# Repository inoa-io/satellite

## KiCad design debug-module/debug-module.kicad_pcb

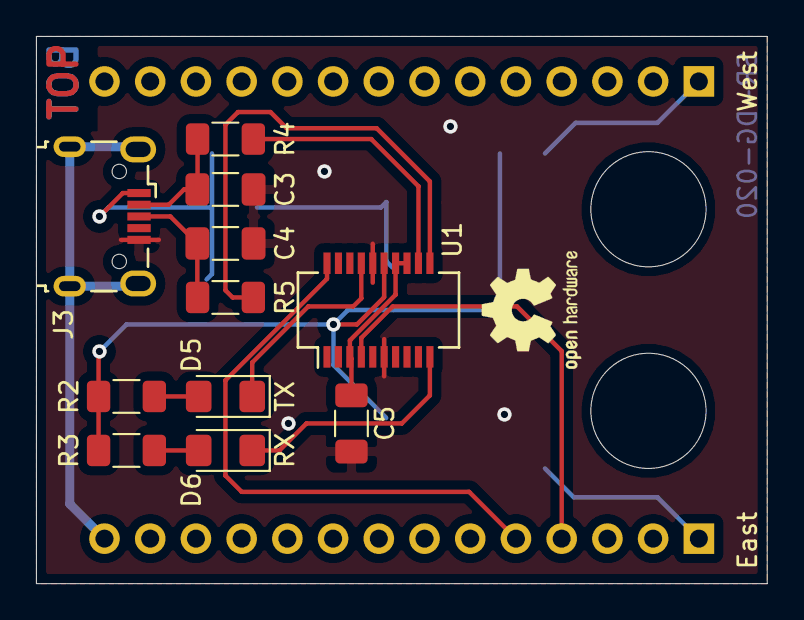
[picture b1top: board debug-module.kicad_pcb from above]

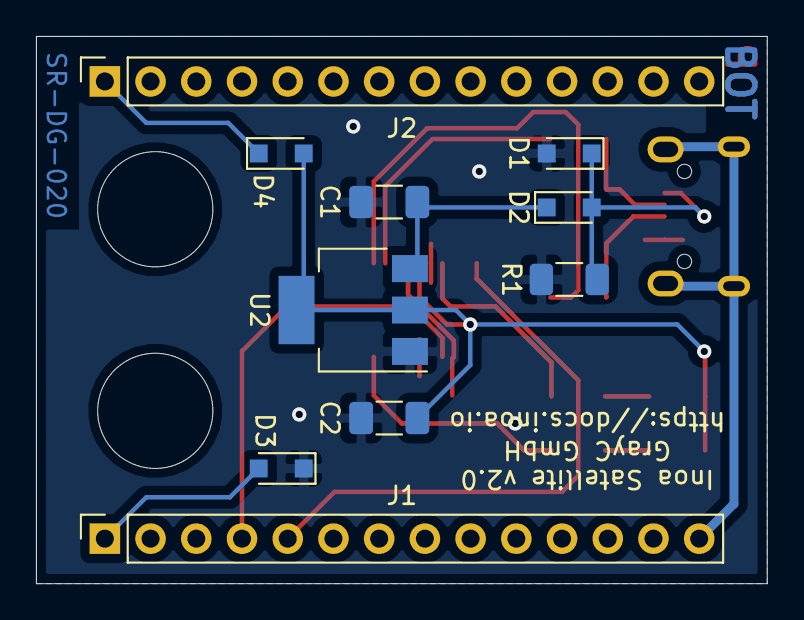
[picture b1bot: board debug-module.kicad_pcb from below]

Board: 2 copper layers, 40.6 x 30.4 mm, 25 parts (11 on the bottom side), 18 nets.

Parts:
C1, C5: 100nF; C_1206_3216Metric_Pad1.33x1.80mm_HandSolder
C2: 10uF; C_1206_3216Metric_Pad1.33x1.80mm_HandSolder
C3, C4: 47pF; C_1206_3216Metric_Pad1.33x1.80mm_HandSolder
D1: BZT52C6V2; D_SOD-323_HandSoldering
D2: 1N5819; D_SOD-323_HandSoldering
D3, D4: D_Schottky; D_SOD-323_HandSoldering
D5: TX; LED_1206_3216Metric_Pad1.42x1.75mm_HandSolder
D6: RX; LED_1206_3216Metric_Pad1.42x1.75mm_HandSolder
G1: LOGO; grayc-logo-negative
G2: Logo_Open_Hardware_Small; OSHW-Logo2_7.3x6mm_SilkScreen
H1: Reset; MountingHole_6.4mm_M6
H2: Status; MountingHole_6.4mm_M6
J1: East; PinSocket_1x14_P2.54mm_Vertical
J2: West; PinSocket_1x14_P2.54mm_Vertical
J3: USB_B_Micro; USB_Micro-B_Wuerth_629105150521
R1: 10k; R_1206_3216Metric_Pad1.30x1.75mm_HandSolder
R2, R3: 220R; R_1206_3216Metric_Pad1.30x1.75mm_HandSolder
R4, R5: 27R; R_1206_3216Metric_Pad1.30x1.75mm_HandSolder
U1: FT231XS; SSOP-20_3.9x8.7mm_P0.635mm
U2: LD1117S33; SOT-223-3_TabPin2

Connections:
+3V3: C2.1, D4.2, R2.1, R3.1, U1.15, U2.2
GND: C1.2, C2.2, C3.2, C4.2, C5.2, D1.2, D3.1, J3.5, R1.2, U1.6, U1.16, U2.1
GNDPWR: J1.14, J3.6
unnamed: C1.1, D2.1, U2.3
unnamed: C5.1, U1.3, U1.13, U1.14
unnamed: D1.1, D2.2, J3.1, R1.1
unnamed: D3.2, J1.1
unnamed: D4.1, J2.1
unnamed: D5.2, R2.2
unnamed: D6.2, R3.2
unnamed: R4.1, U1.12
unnamed: R5.1, U1.11
RX_LED: D6.1, U1.10
TX_LED: D5.1, U1.17
U0RXD: J1.5, U1.20
U0TXD: J1.4, U1.4
USB_DM: C3.1, J3.2, R4.2
USB_DP: C4.1, J3.3, R5.2

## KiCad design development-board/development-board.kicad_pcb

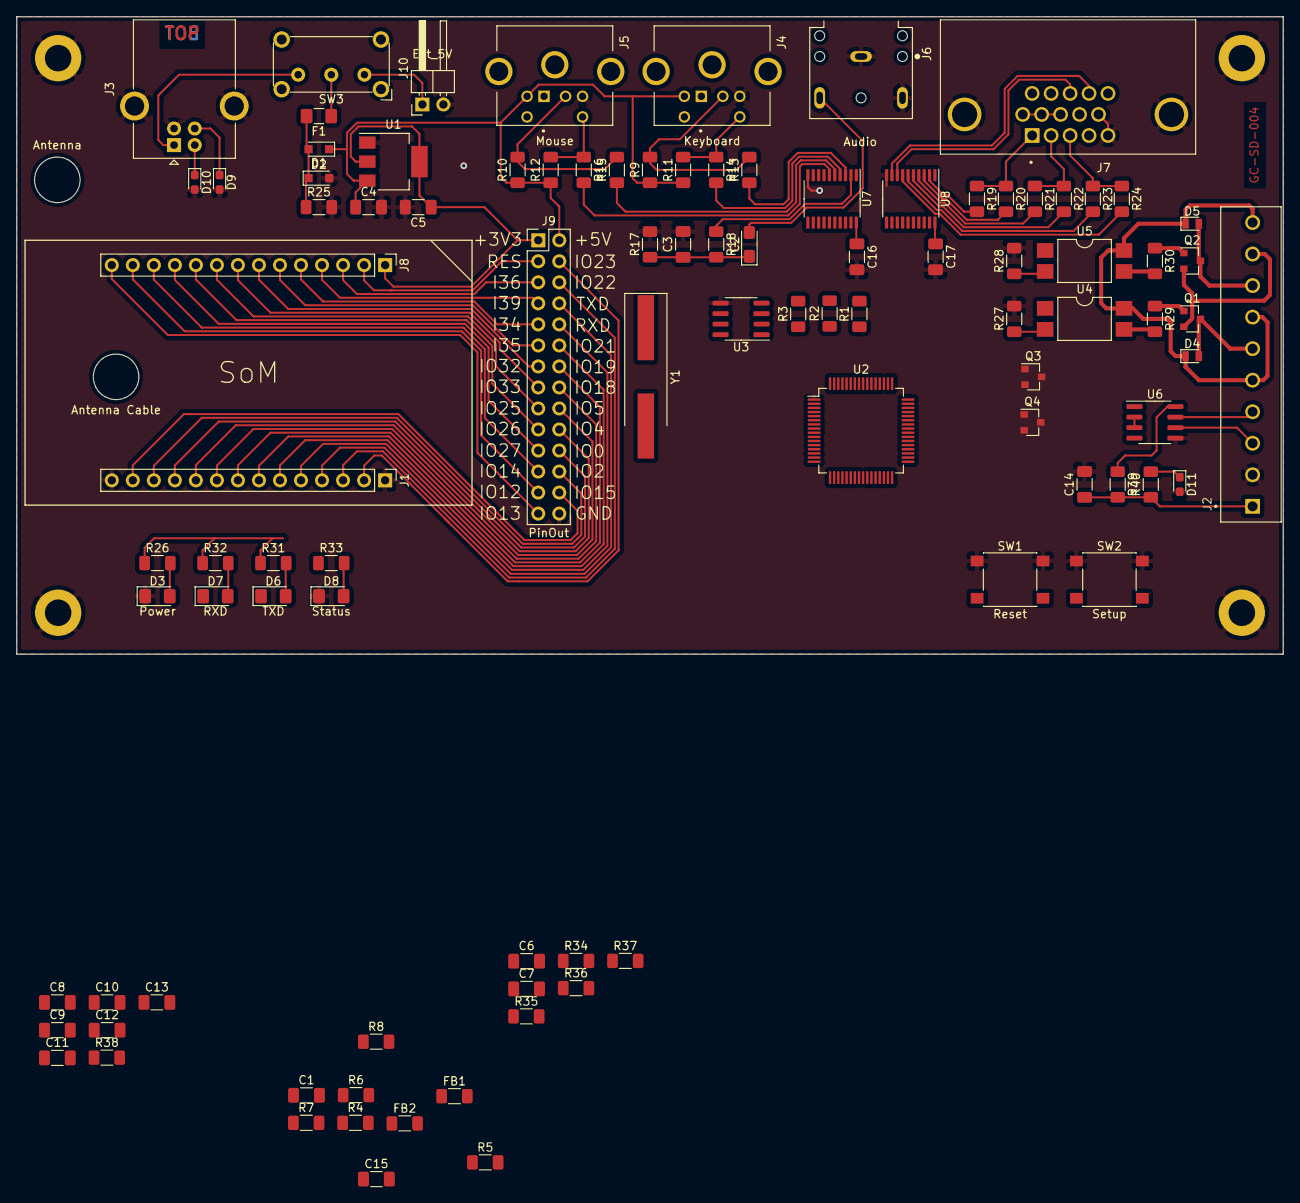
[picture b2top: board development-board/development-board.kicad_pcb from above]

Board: 2 copper layers, 153.0 x 77.0 mm, 103 parts (0 on the bottom side), 95 nets.

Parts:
C1, C3, C4, C14, C15, C16, C17: 100nF; C_1206_3216Metric_Pad1.33x1.80mm_HandSolder
C2: 10uF; CP_EIA-3216-18_Kemet-A_Pad1.58x1.35mm_HandSolder
C5: 10uF; C_1206_3216Metric_Pad1.33x1.80mm_HandSolder
C6, C7: C; C_1206_3216Metric_Pad1.33x1.80mm_HandSolder
C8, C9: 12pF; C_1206_3216Metric_Pad1.33x1.80mm_HandSolder
C10, C12: 4u7; C_1206_3216Metric_Pad1.33x1.80mm_HandSolder
C11, C13: 0u1; C_1206_3216Metric_Pad1.33x1.80mm_HandSolder
D1: BZT52C6V2; D_SOD-323_HandSoldering
D2: 1N5819; D_SOD-323_HandSoldering
D3: Power; LED_1206_3216Metric_Pad1.42x1.75mm_HandSolder
D4, D5: BAV303; D_MicroMELF
D6: TXD; LED_1206_3216Metric_Pad1.42x1.75mm_HandSolder
D7: RXD; LED_1206_3216Metric_Pad1.42x1.75mm_HandSolder
D8: Status; LED_1206_3216Metric_Pad1.42x1.75mm_HandSolder
D9, D10, D11: D_TVS; D_0603_1608Metric_Pad1.05x0.95mm_HandSolder
F1: 6V/800mA; Fuse_1206_3216Metric_Pad1.42x1.75mm_HandSolder
FB1, FB2: 1k@100MHz; R_1206_3216Metric_Pad1.30x1.75mm_HandSolder
H1, H2, H3, H4: MountingHole_Pad; MountingHole_3.2mm_M3_DIN965_Pad
H5: Antenna Cable; MountingHole_5.5mm
H6: Antenna; MountingHole_5.5mm
J1: East; PinHeader_1x14_P2.54mm_Vertical
J2: Screw_Terminal; TE_1-1776113-0
J3: USB_B; USB_B_OST_USB-B1HSxx_Horizontal
J4: Keyboard; TE_5749180-1
J5: Mouse; TE_5749180-1
J6: Audio; CUI_SJ1-3523N
J7: VGA; AMPHENOL_L77HDE15SD1CH4F
J8: West; PinHeader_1x14_P2.54mm_Vertical
J9: PinOut; PinHeader_2x14_P2.54mm_Vertical
J10: Ext_5V; PinHeader_1x02_P2.54mm_Horizontal
Q1, Q2: MMBT3904; SOT-23
Q3, Q4: S8050; SOT-23
R1, R2, R3: 33R; R_1206_3216Metric_Pad1.30x1.75mm_HandSolder
R4, R5, R7, R25, R34, R35, R36, R37: 10k; R_1206_3216Metric_Pad1.30x1.75mm_HandSolder
R6: 2k2; R_1206_3216Metric_Pad1.30x1.75mm_HandSolder
R8: 0R; R_1206_3216Metric_Pad1.30x1.75mm_HandSolder
R9, R10, R11, R12: 2k; R_1206_3216Metric_Pad1.30x1.75mm_HandSolder
R13, R14, R15, R16: 120R; R_1206_3216Metric_Pad1.30x1.75mm_HandSolder
R17: 150R; R_1206_3216Metric_Pad1.30x1.75mm_HandSolder
R18: 270R; R_1206_3216Metric_Pad1.30x1.75mm_HandSolder
R19, R21, R23: 400R; R_1206_3216Metric_Pad1.30x1.75mm_HandSolder
R20, R22, R24: 800R; R_1206_3216Metric_Pad1.30x1.75mm_HandSolder
R26, R27, R28, R29, R30, R31, R32, R33: 220R; R_1206_3216Metric_Pad1.30x1.75mm_HandSolder
R38: 12k; R_1206_3216Metric_Pad1.30x1.75mm_HandSolder
R39, R40: R; R_1206_3216Metric_Pad1.30x1.75mm_HandSolder
SW1: Reset; SW_SPST_PTS645
SW2: Setup; SW_SPST_PTS645
SW3: Power; SW_E-Switch_EG1224_SPDT_Angled
U1: LD1117S33; SOT-223-3_TabPin2
U2: FT2232HL; LQFP-64_10x10mm_P0.5mm
U3: 93C46-WMN6TP; SOIC-8_3.9x4.9mm_P1.27mm
U4, U5: LTV-817S; SMDIP-4_W9.53mm
U6: MAX3486; SOIC-8_3.9x4.9mm_P1.27mm
U7, U8: SN74CBT16292; TSSOP-20_4.4x6.5mm_P0.65mm
Y1: 12MHz; Crystal_SMD_HC49-SD_HandSoldering

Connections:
+3V3: C1.1, C5.1, C15.1, C16.1, C17.1, FB1.1, FB2.2, J8.1, J9.1, R4.2, R5.2, R7.2, R8.1, R26.1, R31.1, R32.1, R34.1, R35.1, R39.1, U1.2, U3.8, U6.8, U7.20, U8.20
+5V: C4.1, D2.1, J4.3, J5.3, J9.2, R9.1, R10.1, R11.1, R12.1, U1.3
Blue_High: R23.2, U8.6
Blue_Low: R24.2, U8.7
Chip_PU: C6.1, J8.2, J9.3, Q4.3, R34.2, SW1.2
EECLK: R2.1, R5.1, U3.2
EECS: R1.1, R4.1, U3.1
EEDATA: R3.1, R6.1, U3.3
FT_~DTR~: Q3.1, R37.1, U2.43
FT_~RTS~: Q4.1, R36.2, U2.40
GND: C1.2, C3.2, C4.2, C5.2, C6.2, C7.2, C8.2, C9.2, C10.2, C11.2, C12.2, C13.2, C14.2, C15.2, C16.2, C17.2, D1.2, D3.1, D8.1, D9.2, D10.2, D11.2, H1.1, H2.1, H3.1, H4.1, J1.1, J1.14, J2.2, J3.4, J3.5, J4.4, J5.4, J6.1, J6.3, J7.0, J7.5, J7.6, J7.7, J7.8, J7.10, J9.28, J10.2, R17.2, R25.2, R27.2, R28.2, R38.2, SW1.1, SW2.1, U1.1, U2.1, U2.5, U2.10, U2.11, U2.13, U2.15, U2.25, U2.35, U2.47, U2.51, U3.5, U6.5, U7.10, U8.10
GND2: J2.9, Q1.2, Q2.2
Green_High: R21.2, U8.4
Green_Low: R22.2, U8.5
HSync: J7.13, U8.8
I34: J8.5, J9.9
I35: J8.6, J9.11
I36: J8.3, J9.5
I39: J8.4, J9.7
IO0: C7.1, J1.11, J9.22, Q3.3, R35.2, SW2.2
IO2: J1.12, J9.24
IO4: J1.10, J9.20, U8.13
IO5: J1.9, J9.18, U8.14
IO12: J8.13, J9.25
IO13: J8.14, J9.27, R33.1
IO14: J8.12, J9.23
IO15: J1.13, J9.26, U8.11
IO18: J1.8, J9.16, U8.15
IO19: J1.7, J9.14, U8.16
IO21: J1.6, J9.12, U8.17
IO22: J1.3, J9.6, U8.18
IO23: J1.2, J9.4, U8.12
IO25: J8.9, J9.17, U7.18
IO26: J8.10, J9.19, U7.15
IO27: J8.11, J9.21, U7.14
IO32: J8.7, J9.13, U7.16
IO33: J8.8, J9.15, U7.17
unnamed: C2.1, C3.1, R17.1, R18.2
unnamed: C2.2, J6.2
unnamed: C8.1, U2.2, Y1.1
unnamed: C9.1, U2.3, Y1.2
unnamed: C10.1, C11.1, FB2.1, U2.4
unnamed: C12.1, C13.1, FB1.2, U2.9
unnamed: D1.1, D2.2, F1.2, R25.1
unnamed: D3.2, R26.2
unnamed: D6.2, R31.2
unnamed: D7.2, R32.2
unnamed: D8.2, R33.2
unnamed: D11.1, R40.2
unnamed: F1.1, SW3.2
unnamed: J4.2, R9.2, R13.2
unnamed: J4.6, R11.2, R14.1
unnamed: J5.2, R10.2, R15.2
unnamed: J5.6, R12.2, R16.1
unnamed: J7.1, R19.1, R20.1
unnamed: J7.2, R21.1, R22.1
unnamed: J7.3, R23.1, R24.1
unnamed: J10.1, SW3.1
unnamed: Q1.1, R29.1
unnamed: Q2.1, R30.1
unnamed: Q3.2, R36.1
unnamed: Q4.2, R37.2
unnamed: R1.2, U2.63
unnamed: R2.2, U2.62
unnamed: R3.2, U2.61
unnamed: R6.2, R7.1, U3.4
unnamed: R8.2, U3.6
unnamed: R27.1, U4.2
unnamed: R28.1, U5.2
unnamed: R29.2, U4.3
unnamed: R30.2, U5.3
unnamed: R38.1, U2.6
PC_Enable: U7.19, U8.19
PS2_0_Clock: R13.1, U7.3
PS2_0_Data: R14.2, U7.4
PS2_1_Clock: R15.1, U7.5
PS2_1_Data: R16.2, U7.6
RS485_A: J2.3, U6.6
RS485_B: J2.4, U6.7
RS485_TXE: U6.2, U6.3
RX_LED: D7.1, U2.54
Red_High: R19.2, U8.2
Red_Low: R20.2, U8.3
Relay_In_0: D4.2, J2.6, Q1.3
Relay_In_1: D5.2, J2.8, Q2.3
S0: C14.1, J2.1, R39.2, R40.1
Speaker: R18.1, U7.2
TX_LED: D6.1, U2.55
U0RXD: J1.5, J9.10
U0TXD: J1.4, J9.8
USB_DN: D10.1, J3.2, U2.7
USB_DP: D9.1, J3.3, U2.8
VBUS: J3.1, SW3.3
VS: D4.1, D5.1, J2.5, J2.7, J2.10, U4.4, U5.4
VSync: J7.14, U8.9

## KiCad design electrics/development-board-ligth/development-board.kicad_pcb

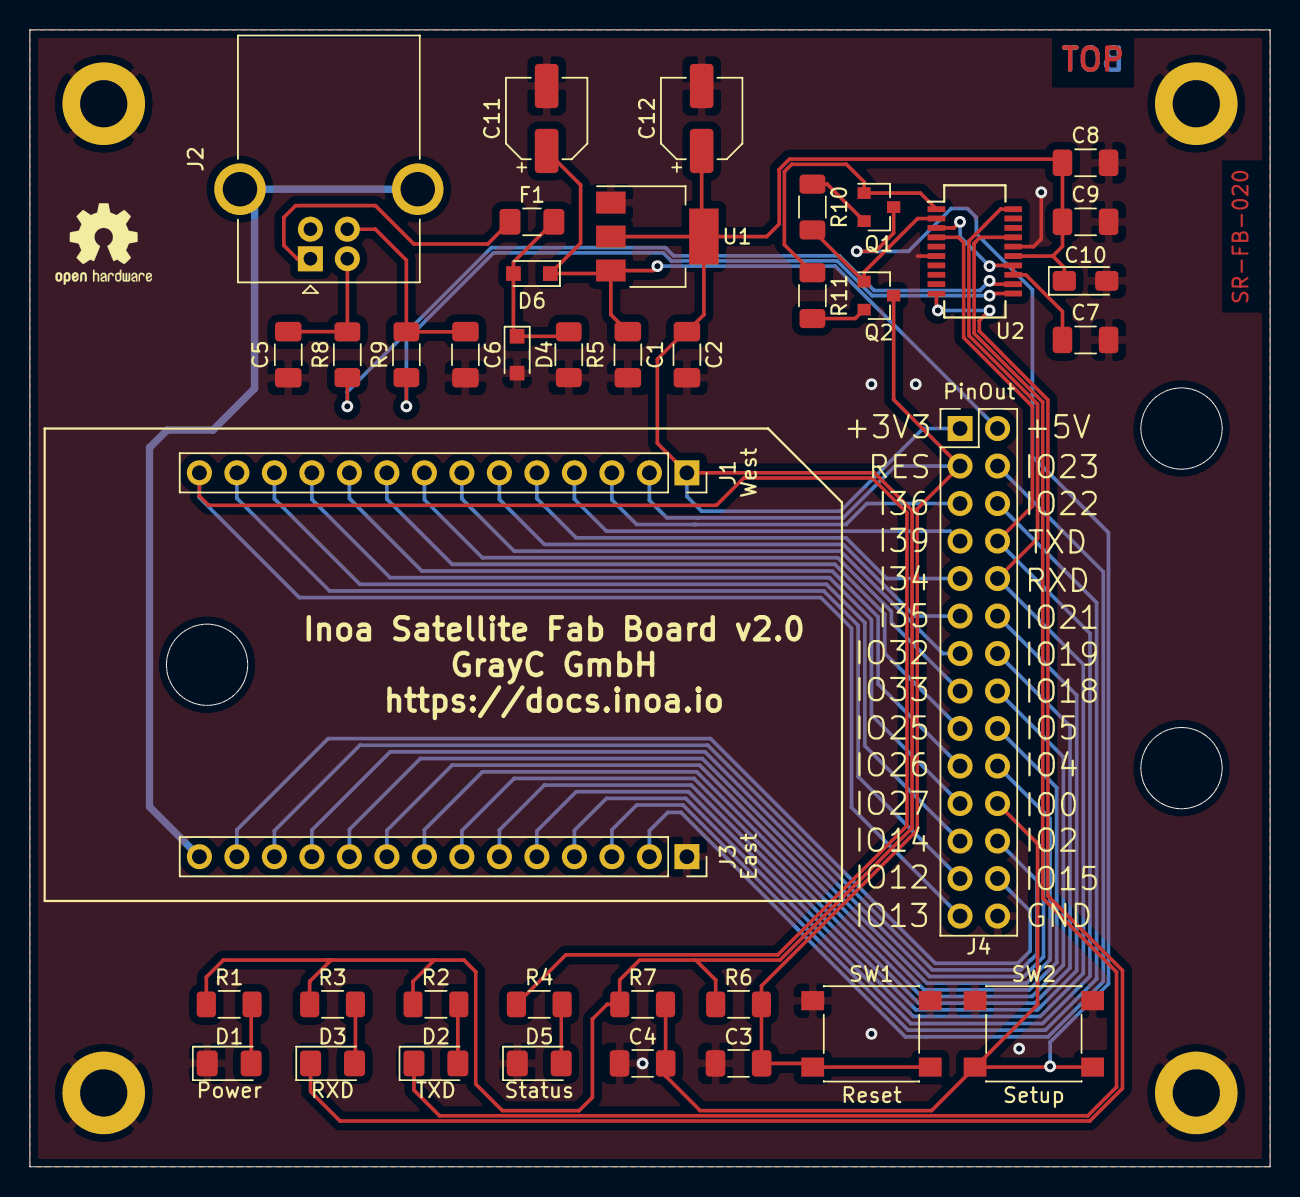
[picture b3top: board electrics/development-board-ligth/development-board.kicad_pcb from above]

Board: 2 copper layers, 84.0 x 77.0 mm, 49 parts (0 on the bottom side), 46 nets.

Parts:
C1, C7, C8, C9: 100nF; C_1206_3216Metric_Pad1.33x1.80mm_HandSolder
C2: 10uF; C_1206_3216Metric_Pad1.33x1.80mm_HandSolder
C3, C4: 1nF; C_1206_3216Metric_Pad1.33x1.80mm_HandSolder
C5, C6: 47pF; C_1206_3216Metric_Pad1.33x1.80mm_HandSolder
C10: 4u7; CP_EIA-3216-18_Kemet-A_Pad1.58x1.35mm_HandSolder
C11: 100uF; CP_Elec_5x5.3
C12: 47uF; CP_Elec_5x5.3
D1: Power; LED_1206_3216Metric_Pad1.42x1.75mm_HandSolder
D2: TXD; LED_1206_3216Metric_Pad1.42x1.75mm_HandSolder
D3: RXD; LED_1206_3216Metric_Pad1.42x1.75mm_HandSolder
D4: BZT52C6V2; D_SOD-323_HandSoldering
D5: Status; LED_1206_3216Metric_Pad1.42x1.75mm_HandSolder
D6: 1N5819; D_SOD-323_HandSoldering
F1: 6V/800mA; Fuse_1206_3216Metric_Pad1.42x1.75mm_HandSolder
H1: WiFi Cable; MountingHole_5.5mm
H2, H3, H5, H7: MountingHole_Pad; MountingHole_3.2mm_M3_DIN965_Pad
H4, H6: Antenna; MountingHole_5.5mm
J1: West; PinSocket_1x14_P2.54mm_Vertical
J2: USB_B; USB_B_OST_USB-B1HSxx_Horizontal
J3: East; PinSocket_1x14_P2.54mm_Vertical
J4: PinOut; PinHeader_2x14_P2.54mm_Vertical
LOGO1: Logo_Open_Hardware_Small; OSHW-Logo2_7.3x6mm_SilkScreen
LOGO2: LOGO; grayc-logo-negative
Q1, Q2: S8050; SOT-23
R1, R2, R3, R4: 220R; R_1206_3216Metric_Pad1.30x1.75mm_HandSolder
R5, R6, R7, R10, R11: 10k; R_1206_3216Metric_Pad1.30x1.75mm_HandSolder
R8, R9: 27R; R_1206_3216Metric_Pad1.30x1.75mm_HandSolder
SW1: Reset; SW_SPST_PTS645
SW2: Setup; SW_SPST_PTS645
U1: LD1117S33; SOT-223-3_TabPin2
U2: FT231XS; SSOP-20_3.9x8.7mm_P0.635mm

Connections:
+3V3: C2.1, C8.1, C9.1, C10.1, C12.1, J1.1, J4.1, R1.1, R2.1, R3.1, R6.1, R7.1, U1.2, U2.15
+5V: C1.1, C11.1, D6.1, J4.2, U1.3
Chip_PU: C3.1, J1.2, J4.3, Q2.3, R6.2, SW1.2
FT_~DTR: Q1.1, R11.1, U2.1
FT_~RTS: Q2.1, R10.2, U2.2
GND: C1.2, C2.2, C3.2, C4.2, C5.2, C6.2, C7.2, C8.2, C9.2, C10.2, C11.2, C12.2, D1.1, D4.2, D5.1, H2.1, H3.1, H5.1, H7.1, J2.4, J3.1, J4.28, R5.2, SW1.1, SW2.1, U1.1, U2.6, U2.16
GNDPWR: J2.5, J3.14
I34: J1.5, J4.9
I35: J1.6, J4.11
I36: J1.3, J4.5
I39: J1.4, J4.7
IO0: C4.1, J3.11, J4.22, Q1.3, R7.2, SW2.2
IO2: J3.12, J4.24
IO4: J3.10, J4.20
IO5: J3.9, J4.18
IO12: J1.13, J4.25
IO13: J1.14, J4.27, R4.1
IO14: J1.12, J4.23
IO15: J3.13, J4.26
IO18: J3.8, J4.16
IO19: J3.7, J4.14
IO21: J3.6, J4.12
IO22: J3.3, J4.6
IO23: J3.2, J4.4
IO25: J1.9, J4.17
IO26: J1.10, J4.19
IO27: J1.11, J4.21
IO32: J1.7, J4.13
IO33: J1.8, J4.15
unnamed: C7.1, U2.3, U2.13, U2.14
unnamed: D1.2, R1.2
unnamed: D2.2, R2.2
unnamed: D3.2, R3.2
unnamed: D4.1, D6.2, F1.2, R5.1
unnamed: D5.2, R4.2
unnamed: Q1.2, R10.1
unnamed: Q2.2, R11.2
unnamed: R8.1, U2.12
unnamed: R9.1, U2.11
RX_LED: D3.1, U2.10
TX_LED: D2.1, U2.17
U0RXD: J3.5, J4.10, U2.20
U0TXD: J3.4, J4.8, U2.4
USB_DM: C5.1, J2.2, R8.2
USB_DP: C6.1, J2.3, R9.2
VBUS: F1.1, J2.1

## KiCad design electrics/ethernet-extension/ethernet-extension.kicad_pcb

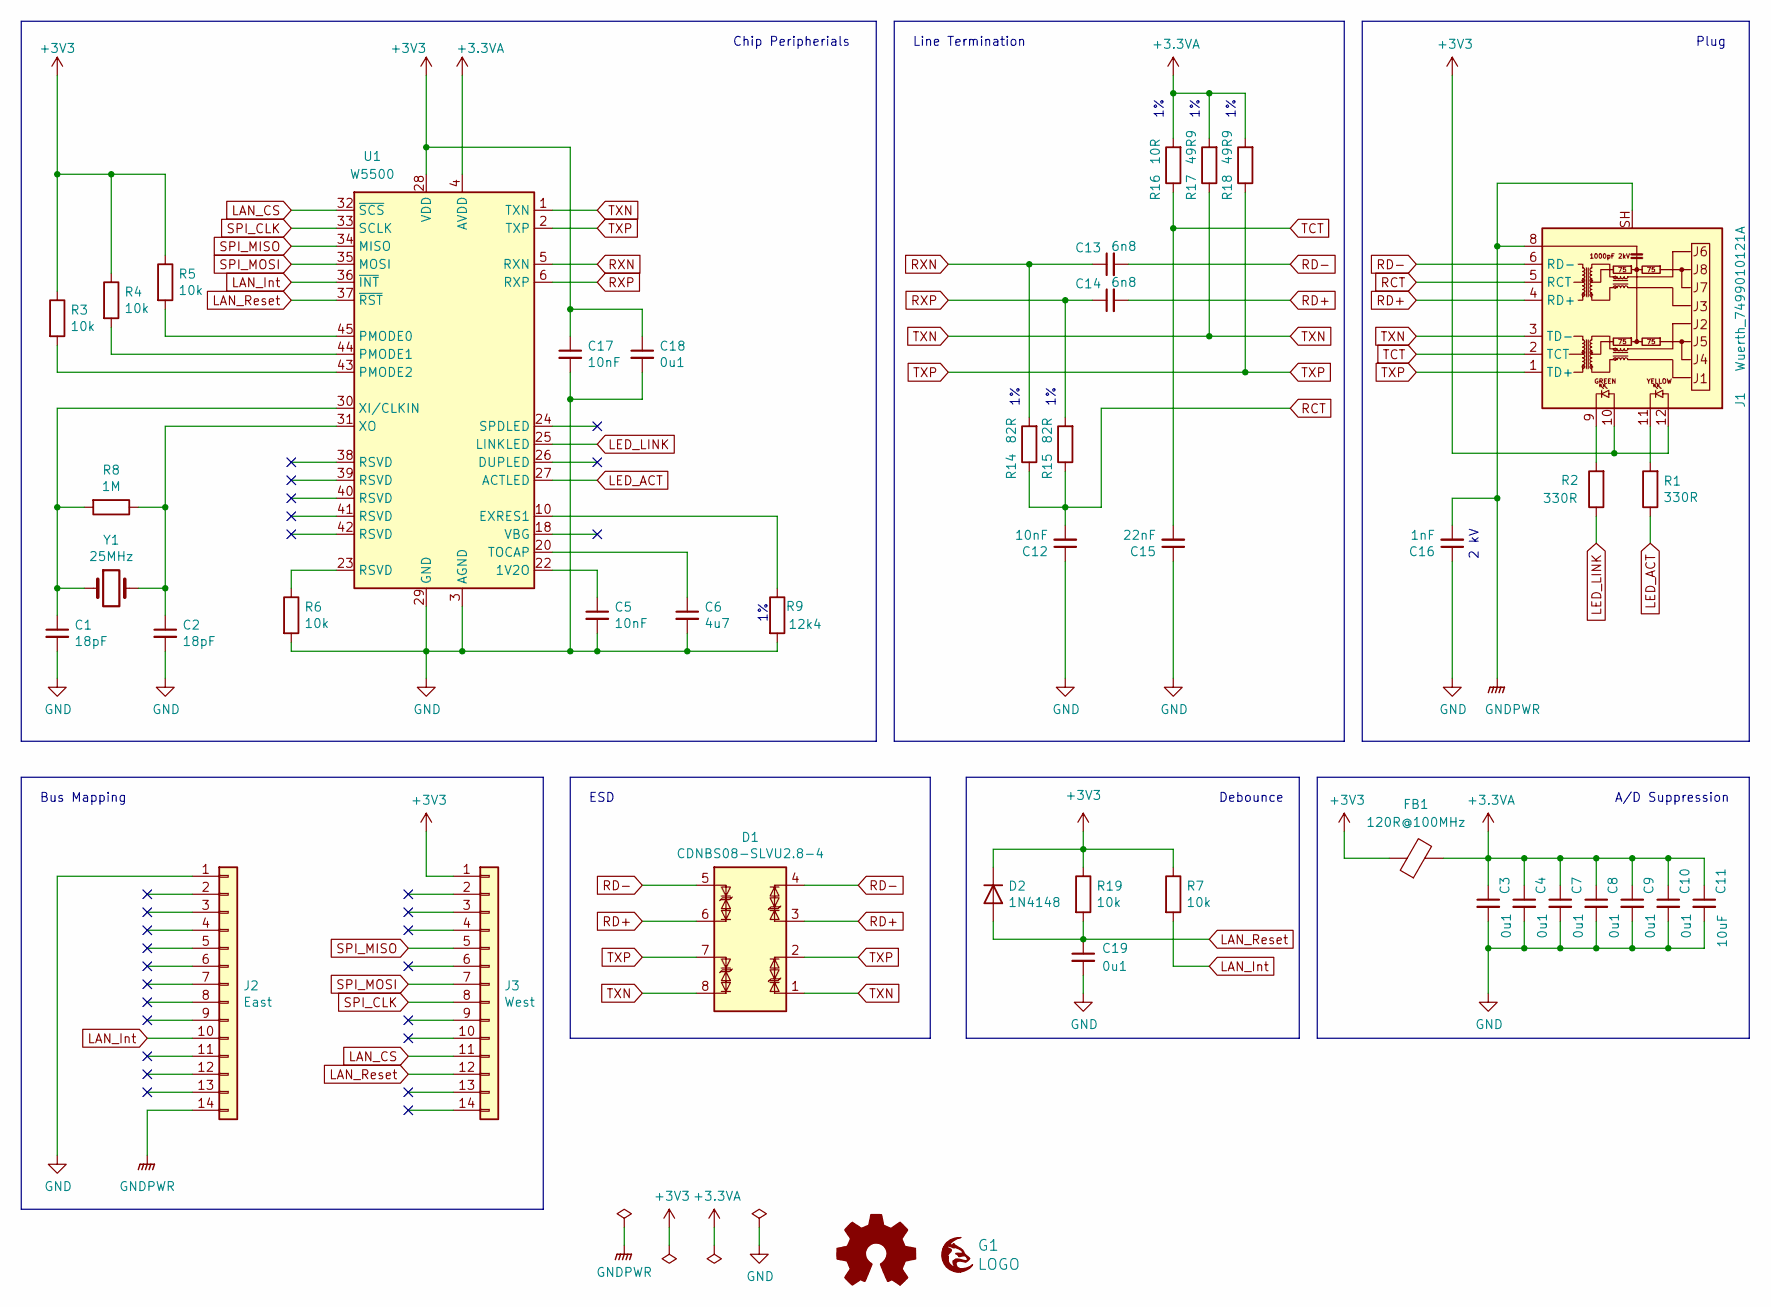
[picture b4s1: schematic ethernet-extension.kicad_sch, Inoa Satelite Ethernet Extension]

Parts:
C1, C2: 18pF; C_0603_1608Metric_Pad1.08x0.95mm_HandSolder; mouser# 581-06035A180JAT4A
C3, C4, C7, C8, C9, C10, C18, C19: 0u1; C_0603_1608Metric_Pad1.08x0.95mm_HandSolder; mouser# 80-C0603C104M4R
C5, C12, C17: 10nF; C_0603_1608Metric_Pad1.08x0.95mm_HandSolder; mouser# 581-06031C103K4T2A
C6: 4u7; C_0603_1608Metric_Pad1.08x0.95mm_HandSolder; mouser# 187-CL10A475MQ8NNNC
C11: 10uF; C_0603_1608Metric_Pad1.08x0.95mm_HandSolder; mouser# 187-CL10A106MQ8NNNC
C13, C14: 6n8; C_0603_1608Metric_Pad1.08x0.95mm_HandSolder; mouser# 80-C0603C682K5R
C15: 22nF; C_0603_1608Metric_Pad1.08x0.95mm_HandSolder; mouser# 187-CL10B223KB8NNNC
C16: 1nF; C_1812_4532Metric_Pad1.57x3.40mm_HandSolder; mouser# 80-C1812C103KGR
D1: CDNBS08-SLVU2.8-4; SOIC-8_3.9x4.9mm_P1.27mm; mouser# 652-CDNBS08SLVU2.8-4
D2: 1N4148; D_SOD-323_HandSoldering; mouser# 241-1N4148WSR100001
FB1: 120R@100MHz; L_0805_2012Metric; mouser# 652-MG2029-121Y
G1: LOGO; grayc-logo-negative
G2: Logo_Open_Hardware_Small; OSHW-Logo2_7.3x6mm_SilkScreen
J1: Wuerth_7499010121A; RJ45_Wuerth_7499010121A_Horizontal; mouser# 710-7499010121A
J2: East; PinHeader_1x14_P2.54mm_Vertical; mouser# 437-8018701453001101
J3: West; PinHeader_1x14_P2.54mm_Vertical; mouser# 437-8018701453001101
R1, R2: 330R; R_0603_1608Metric_Pad0.98x0.95mm_HandSolder; mouser# 652-CR0603FX-3300ELF
R3, R4, R5, R6, R7, R19: 10k; R_0603_1608Metric_Pad0.98x0.95mm_HandSolder; mouser# 652-CR0603AFX1002EAS
R8: 1M; R_0603_1608Metric_Pad0.98x0.95mm_HandSolder; mouser# 652-CMP0603-FX-1004L
R9: 12k4; R_0603_1608Metric_Pad0.98x0.95mm_HandSolder; mouser# 652-CR0603FX-1242ELF
R14, R15: 82R; R_0603_1608Metric_Pad0.98x0.95mm_HandSolder; mouser# 667-ERJ-3EKF82R0V
R16: 10R; R_0603_1608Metric_Pad0.98x0.95mm_HandSolder; mouser# 603-RC0603FR-1310RL
R17, R18: 49R9; R_0603_1608Metric_Pad0.98x0.95mm_HandSolder; mouser# 667-ERJ-3EKF49R9V
U1: W5500; LQFP-48_7x7mm_P0.5mm; mouser# 950-W5500
Y1: 25MHz; Crystal_SMD_0603-2Pin_6.0x3.5mm_HandSoldering; mouser# 520-250-18-23A

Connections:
+3.3VA: C3.1, C4.1, C7.1, C8.1, C9.1, C10.1, C11.1, FB1.2, R16.2, R17.2, R18.2, U1.4 (AVDD), U1.8 (AVDD), U1.11 (AVDD), U1.15 (AVDD), U1.17 (AVDD), U1.21 (AVDD)
+3V3: C17.1, C18.1, D2.1 (K), FB1.1, J1.10, J1.12, J3.1, R3.1, R4.1, R5.1, R7.1, R19.1, U1.28 (VDD)
GND: C1.2, C2.2, C3.2, C4.2, C5.2, C6.2, C7.2, C8.2, C9.2, C10.2, C11.2, C12.1, C15.1, C16.1, C17.2, C18.2, C19.2, J2.1, R6.2, R9.2, U1.3 (AGND), U1.9 (AGND), U1.14 (AGND), U1.16 (AGND), U1.19 (AGND), U1.29 (GND), U1.48 (AGND)
GNDPWR: C16.2, J1.8, J1.SH, J2.14
LAN_CS: J3.11, U1.32 (~SCS)
LAN_Int: J2.10, R7.2, U1.36 (~INT)
LAN_Reset: C19.1, D2.2 (A), J3.12, R19.2, U1.37 (~RST)
LED_ACT: R1.1, U1.27 (ACTLED)
LED_LINK: R2.1, U1.25 (LINKLED)
unnamed: C1.1, R8.2, U1.30 (XI/CLKIN), Y1.1
unnamed: C2.1, R8.1, U1.31 (XO), Y1.2
unnamed: C5.1, U1.22 (1V2O)
unnamed: C6.1, U1.20 (TOCAP)
unnamed: J1.9, R2.2
unnamed: J1.11, R1.2
unnamed: R3.2, U1.43 (PMODE2)
unnamed: R4.2, U1.44 (PMODE1)
unnamed: R5.2, U1.45 (PMODE0)
unnamed: R6.1, U1.23 (RSVD)
unnamed: R9.1, U1.10 (EXRES1)
RCT: C12.2, J1.5 (RCT), R14.1, R15.1
RD+: C14.2, D1.3 (TVS1), D1.6 (TVS2), J1.4 (RD+)
RD-: C13.2, D1.4 (TVS2), D1.5 (TVS1), J1.6 (RD-)
RXN: C13.1, R14.2, U1.5 (RXN)
RXP: C14.1, R15.2, U1.6 (RXP)
SPI_CLK: J3.8, U1.33 (SCLK)
SPI_MISO: J3.5, U1.34 (MISO)
SPI_MOSI: J3.7, U1.35 (MOSI)
TCT: C15.2, J1.2 (TCT), R16.1
TXN: D1.1 (TVS1), D1.8 (TVS2), J1.3 (TD-), R17.1, U1.1 (TXN)
TXP: D1.2 (TVS2), D1.7 (TVS1), J1.1 (TD+), R18.1, U1.2 (TXP)

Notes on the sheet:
ESD
Debounce
2 kV
A/D Suppression
Chip Peripherials
Plug
Line Termination
Bus Mapping

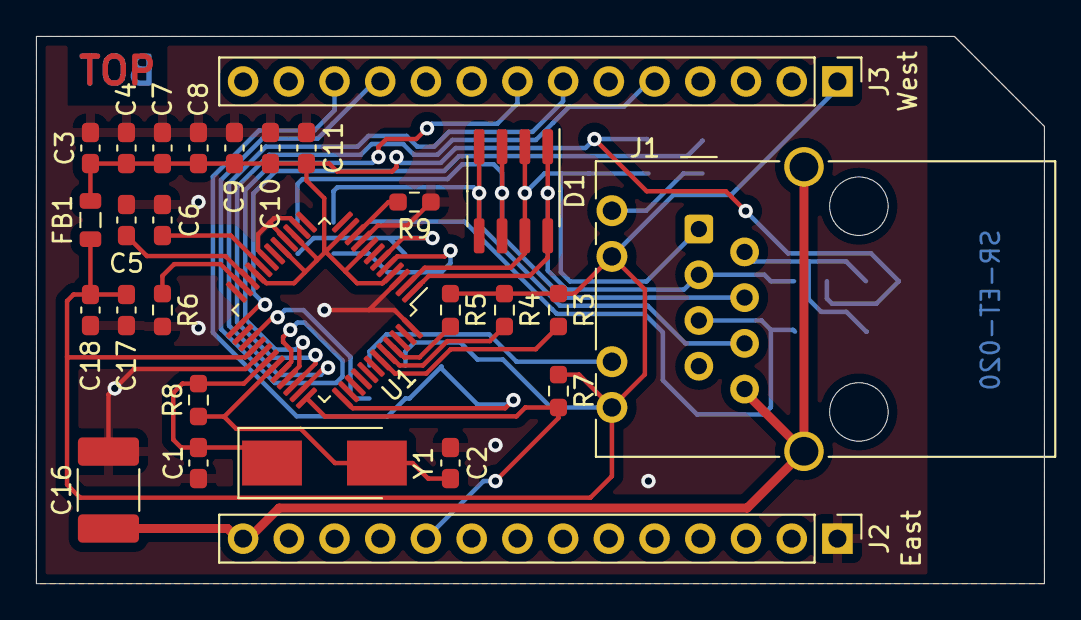
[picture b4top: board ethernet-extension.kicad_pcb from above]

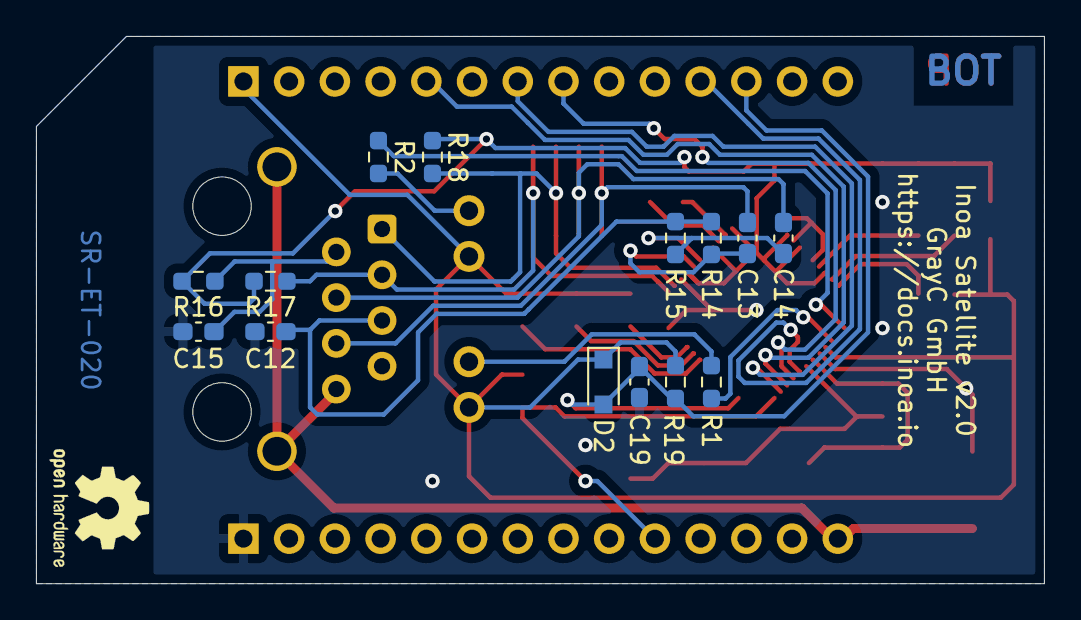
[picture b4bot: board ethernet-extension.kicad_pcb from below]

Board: 2 copper layers, 56.0 x 30.4 mm, 44 parts (16 on the bottom side), 31 nets.

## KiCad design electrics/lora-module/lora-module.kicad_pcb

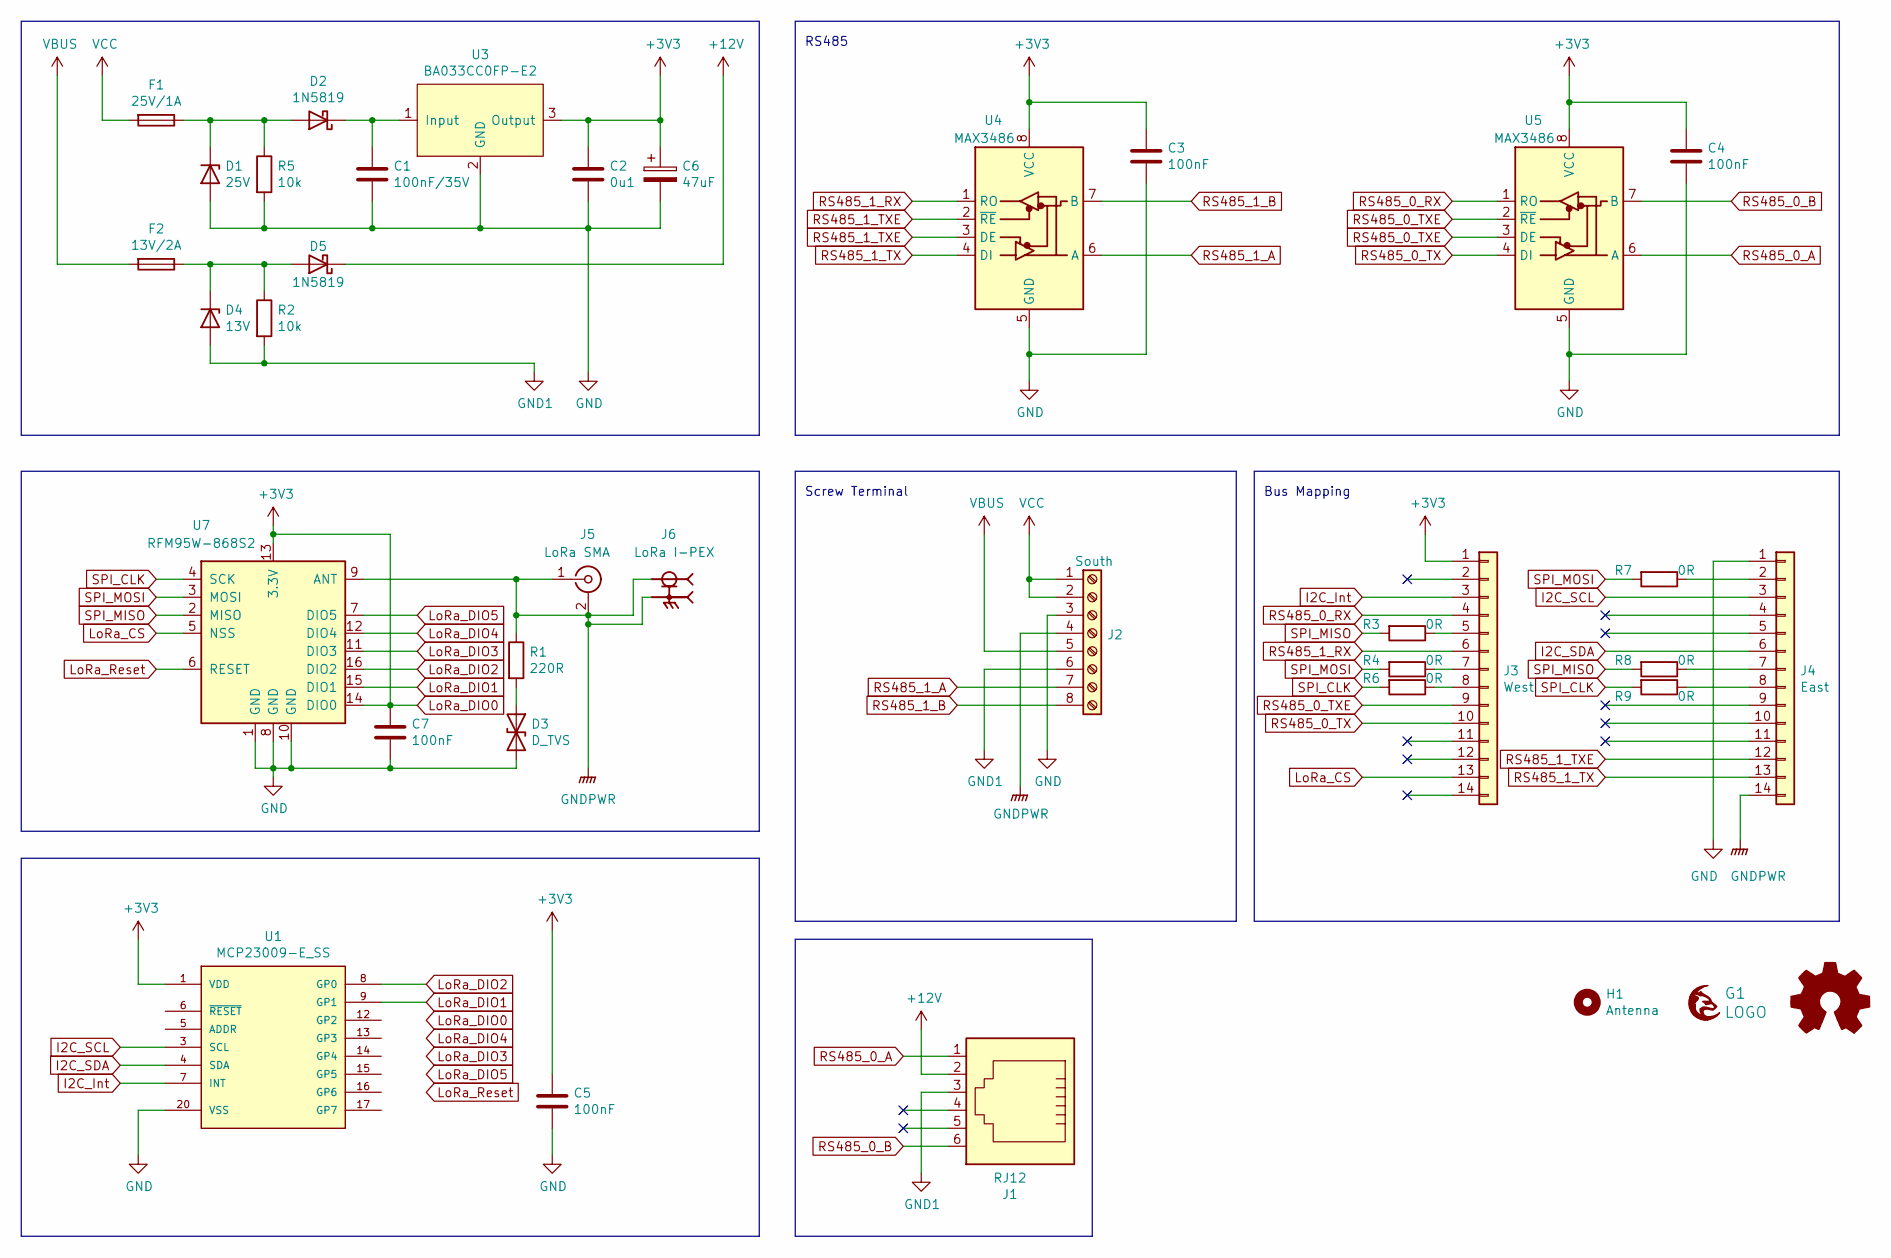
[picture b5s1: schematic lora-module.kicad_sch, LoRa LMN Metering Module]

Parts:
C1: 100nF/35V; C_1206_3216Metric_Pad1.33x1.80mm_HandSolder
C2: 0u1; C_1206_3216Metric_Pad1.33x1.80mm_HandSolder
C3, C4, C5, C7: 100nF; C_1206_3216Metric_Pad1.33x1.80mm_HandSolder
C6: 47uF; CP_Elec_5x5.3
D1: 25V; D_SOD-523
D2, D5: 1N5819; D_SOD-323_HandSoldering
D3: D_TVS; D_0603_1608Metric_Pad1.05x0.95mm_HandSolder
D4: 13V; D_SOD-523
F1: 25V/1A; Fuse_1206_3216Metric_Pad1.42x1.75mm_HandSolder
F2: 13V/2A; Fuse_1206_3216Metric_Pad1.42x1.75mm_HandSolder
G1: LOGO; grayc-logo-negative
G2: Logo_Open_Hardware_Small; OSHW-Logo2_7.3x6mm_SilkScreen
H1: Antenna; MountingHole_3.7mm
J1: RJ12; CUI_CRJ030-G-TH
J2: South; PHOENIX_1727078
J3: West; PinHeader_1x14_P2.54mm_Vertical
J4: East; PinHeader_1x14_P2.54mm_Vertical
J5: LoRa SMA; LINX_CONSMA002
J6: LoRa I-PEX; SAMTEC_RSP-122811-01; PARTREV H
R1: 220R; R_1206_3216Metric_Pad1.30x1.75mm_HandSolder
R2, R5: 10k; R_1206_3216Metric_Pad1.30x1.75mm_HandSolder
R3, R4, R6, R7, R8, R9: 0R; R_1206_3216Metric_Pad1.30x1.75mm_HandSolder
U1: MCP23009-E_SS; SOP65P780X200-20N; PARTREV C
U3: BA033CC0FP-E2; TO-252-3_TabPin2
U4, U5: MAX3486; SOIC-8_3.9x4.9mm_P1.27mm
U7: RFM95W-868S2; XCVR_RFM69HW-868S2

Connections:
+12V: D5.1 (K), J1.2
GND: C1.2, C2.2, C3.2, C4.2, C5.2, C6.2, C7.2, D1.2 (A), D3.2 (A2), J2.3, J4.1, R5.2, U1.20 (VSS), U3.2 (GND), U4.5 (GND), U5.5 (GND), U7.1 (GND), U7.8 (GND), U7.10 (GND)
GND1: D4.2 (A), J1.3, J2.6, R2.2
I2C_Int: J3.3, U1.7 (INT)
I2C_SCL: J4.3, U1.3 (SCL)
I2C_SDA: J4.6, U1.4 (SDA)
LoRa_CS: J3.13, U7.5 (NSS)
LoRa_DIO1: U1.9 (GP1), U7.15 (DIO1)
LoRa_DIO2: U1.8 (GP0), U7.16 (DIO2)
LoRa_DIO3: U7.11 (DIO3)
LoRa_DIO4: U7.12 (DIO4)
LoRa_DIO5: U7.7 (DIO5)
LoRa_Reset: U7.6 (RESET)
unnamed: C1.1, D2.1 (K), U3.1 (Input)
unnamed: D1.1 (K), D2.2 (A), F1.1, R5.1
unnamed: D3.1 (A1), R1.2
unnamed: D4.1 (K), D5.2 (A), F2.1, R2.1
unnamed: J3.5, R3.1
unnamed: J3.7, R4.1
unnamed: J3.8, R6.1
unnamed: J4.2, R7.1
unnamed: J4.7, R8.1
unnamed: J4.8, R9.1
RS485_0_A: J1.1, U5.6 (A)
RS485_0_B: J1.6, U5.7 (B)
RS485_0_RX: J3.4, U5.1 (RO)
RS485_0_TX: J3.10, U5.4 (DI)
RS485_0_TXE: J3.9, U5.2 (~RE), U5.3 (DE)
RS485_1_A: J2.7, U4.6 (A)
RS485_1_B: J2.8, U4.7 (B)
RS485_1_RX: J3.6, U4.1 (RO)
RS485_1_TX: J4.13, U4.4 (DI)
RS485_1_TXE: J4.12, U4.2 (~RE), U4.3 (DE)
SPI_CLK: R6.2, R9.2, U7.4 (SCK)
SPI_MISO: R3.2, R8.2, U7.2 (MISO)
SPI_MOSI: R4.2, R7.2, U7.3 (MOSI)
VBUS: F2.2, J2.5
VCC: F1.2, J2.1, J2.2

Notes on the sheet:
RS485
Bus Mapping
Screw Terminal

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
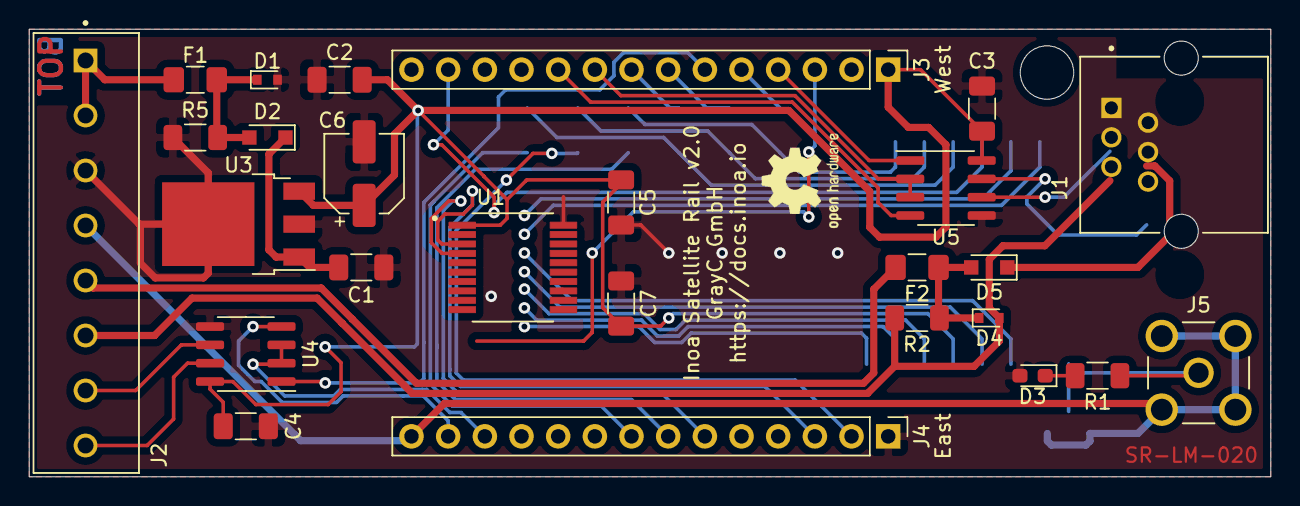
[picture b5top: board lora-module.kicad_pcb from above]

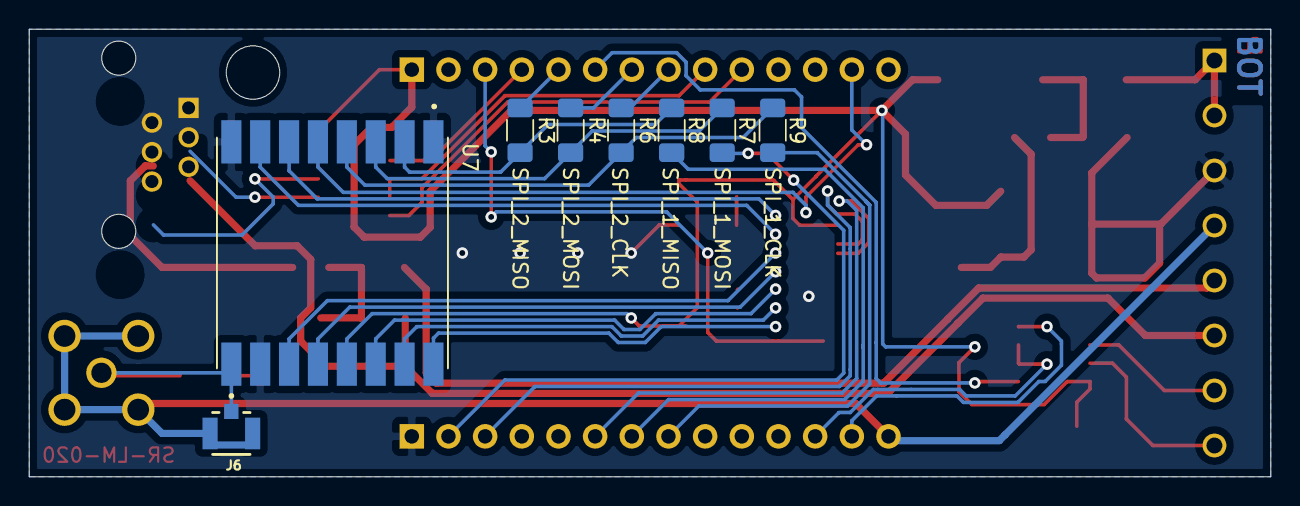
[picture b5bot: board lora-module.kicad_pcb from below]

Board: 2 copper layers, 86.0 x 31.0 mm, 37 parts (8 on the bottom side), 37 nets.
